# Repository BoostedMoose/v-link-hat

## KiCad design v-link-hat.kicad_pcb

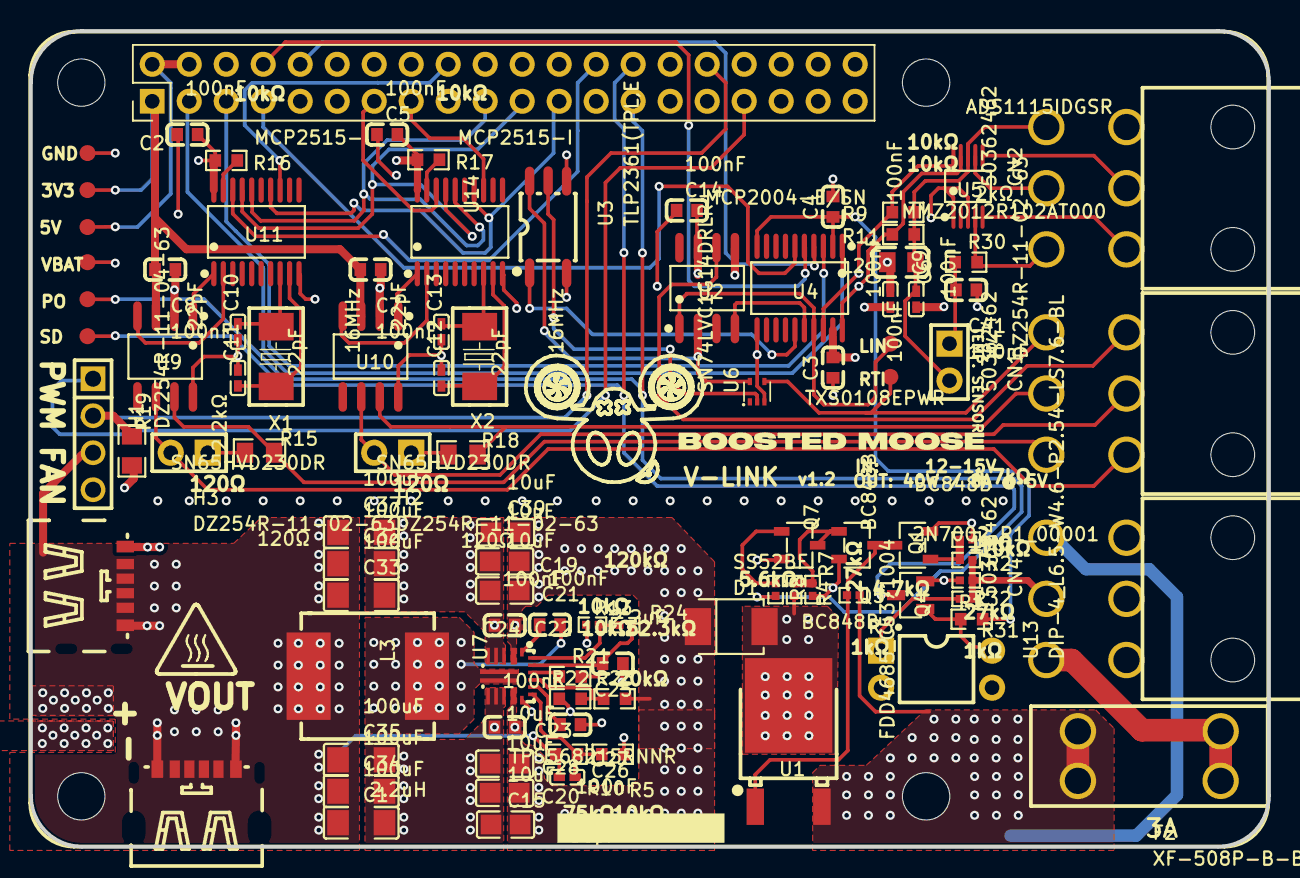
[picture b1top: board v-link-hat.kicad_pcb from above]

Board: 4 copper layers, 85.0 x 56.0 mm, 96 parts (0 on the bottom side), 69 nets.

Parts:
C1, C32, C33, C34, C35, C37: 100uF; C1206
C2, C3, C4, C5, C7, C8, C14, C22, C23, C24, C27, C41: 100nF; C0603
C6, C9: 100nF; C0402
C10, C11, C12, C13: 22pF; C0402
C15, C19, C20, C21, C28, C39: 10uF; C0805
C25: 2.2uF; C0603
C26: 50pF; C0402
CN1, CN2, CN4: 50362462; CONN-TH_50362462
D1: SS52BF; SMBF_L4.3-W3.6-LS5.3-RD
F2: XF-508P-B-B; FUSE-TH_4P-L16.0-W6.7
H1: DZ254R-11-04-63; HDR-TH_4P-P2.54-V-M
H2, H3, H4: DZ254R-11-02-63; HDR-TH_2P-P2.54-V-M-1
L2: MMZ2012R102AT000; L0805
L3: 2.2uH; IND-SMD_L8.0-W8.0-1
Pad_gge54079: Pad_gge54079
Pad_gge54130: Pad_gge54130
Pad_gge54154: Pad_gge54154
Pad_gge54178: Pad_gge54178
Pad_gge54202: Pad_gge54202
Pad_gge54226: Pad_gge54226
Pad_gge90525: Pad_gge90525
Pad_gge90570: Pad_gge90570
Q1, Q5, Q7: BC848B; SOT-23-3_L2.9-W1.6-P1.90-LS2.8-BR
Q4: 2N7002_R1_00001; SOT-23-3_L2.9-W1.3-P1.90-LS2.4-BR
R1: 1MΩ; R0402
R2, R8: 27kΩ; R0402
R3, R31: 1kΩ; R0402
R4, R6: 4.7kΩ; R0402
R5, R9, R11, R16, R17, R21, R22, R32: 10kΩ; R0603
R7: 5.6kΩ; R0402
R10: 75kΩ; R0603
R13: 120kΩ; R0402
R15, R18: 120Ω; R0805
R19: 2.2kΩ; R0805
R23: 52.3kΩ; R0603
R24: 20kΩ; R0402
R30: 2kΩ; R0603
U1: FDD4685_C5371004; TO-252-3_L6.6-W6.1-P4.57-LS9.9-BR-CW
U2: MCP2004-E/SN; SOIC-8_L4.9-W3.9-P1.27-LS6.0-BL
U3: TLP2361(TPL,E; OPTO-SMD-5_L3.7-W4.6-P1.27-LS7.0-BR
U4: TXS0108EPWR; TSSOP-20_L6.5-W4.4-P0.65-LS6.4-BL
U5: ADS1115IDGSR; MSOP-10_L3.0-W3.0-P0.50-LS5.0-BL
U6: SN74LVC1G14DRLR; SOT-553-5_L1.6-W1.2-P0.50-LS1.6-TL
U7: TPS568215RNNR; VQFN-HR-18_L3.5-W3.5-P0.55-BL_TPS56C215RNNR
U8: RASPBERRY PI 4B
U9, U10: SN65HVD230DR; SOIC-8_L4.9-W3.9-P1.27-LS6.0-BL
U11, U14: MCP2515-I; TSSOP-20_L6.5-W4.4-P0.65-LS6.4-BL
U13: DIP-4_L6.5-W4.6-P2.54-LS7.6-BL
USB1, USB2: TYPE-C 6P(073); TYPE-C-SMD_TYPE-C-6P
X1, X2: 16MHz; OSC-SMD_L5.0-W3.2

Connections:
3.3V_PI: C2.2, C4.2, C5.2, C7.2, C8.2, Pad_gge54130.1, R16.1, R17.1, R19.2, R32.2, U4.2, U4.10, U8.1, U8.17, U9.3, U10.3, U11.20, U14.20
5V_RPI: C3.1, C6.1, L2.1, Pad_gge54154.1, U2.2, U3.6, U4.19, U6.5, U8.2, U8.4
!RTI_RX_5V: U3.5, U6.2
AVDD: C9.2, CN2.4, H4.2, L2.2, R9.2, R11.2, U5.8
A_IN_0: CN2.6, R30.2, U5.4
A_IN_1: CN2.3, U5.5
A_IN_2: CN2.2, U5.6
A_IN_3: CN2.5, U5.7
C12_2: C12.2, U14.9, X2.2
C13_2: C13.2, U14.8, X2.1
CAN1_H: CN1.6, R15.1, U9.7
CAN1_L: CN1.3, H3.2, U9.6
CAN2_H: CN1.5, R18.1, U10.7
CAN2_L: CN1.2, H2.2, U10.6
CE1: U8.26, U11.18
CE2: U8.13, U14.18
FB: C26.1, R5.2, R10.1, U7.13
GND: C1.2, C2.1, C3.2, C4.1, C5.1, C6.2, C7.1, C8.1, C9.1, C10.1, C11.1, C12.1, C13.1, C14.1, C15.1, C19.1, C20.1, C21.1, C22.1, C23.1, C25.2, C27.1, C28.1, C32.2, C33.2, C34.2, C35.2, C37.2, C39.1, C41.1, CN2.1, CN4.1, CN4.2, CN4.3, H1.4, Pad_gge54079.1, Q1.2, Q4.2, Q5.2, Q7.2, R1.1, R4.2, R5.1, R6.2, R13.1, R22.1, U2.5, U3.3, U3.4, U4.11, U5.1, U5.3, U6.3, U7.3, U7.4, U7.5, U7.8, U7.9, U7.10, U7.12, U8.6, U8.9, U8.14, U8.20, U8.25, U8.30, U8.34, U8.39, U9.2, U9.8, U10.2, U10.8, U11.10, U13.2, U13.3, U14.10, USB1.A12, USB1.B12, USB2.A12, USB2.B12
GPIO_POWEROFF: Pad_gge54202.1, R8.2, U8.27
GPIO_SHUTDOWN: Pad_gge54226.1, Q4.3, U8.28
H4_1: C41.2, H4.1, R30.1
IGN: CN4.5, R1.2, R2.1, R31.1
IGN_HAT: Q4.1, R32.1, U13.4
IGN_OPTO: R31.2, U13.1
INT_1: U8.18, U11.13
INT_2: U8.15, U14.13
LIN: CN1.1, U2.6
LIN_RX_3V: U4.4, U8.10
LIN_RX_5V: Pad_gge90525.1, U2.1, U4.17
LIN_TX_3V: U4.5, U8.8
LIN_TX_5V: U2.4, U4.16
MISO: U8.21, U11.17, U14.17
MOSI: U8.19, U11.16, U14.16
PWM: H1.1, U8.33
R2_2: Q1.1, R2.2, R6.1
R3_1: F2.2, F2.3, R3.1, U1.3
R3_2: Q1.3, Q5.3, R3.2, U1.1
R4_1: Q5.1, Q7.3, R4.1, R7.2
R7_1: D1.2, R7.1, U1.2
R8_1: Q7.1, R8.1
R15_2: H3.1, R15.2
R17_2: R17.2, U14.19
R18_2: H2.1, R18.2
RTI_RX: CN1.4, Pad_gge90570.1, U6.4
RTI_RX_3V: U4.6, U8.7
RTI_RX_5V: U3.1, U4.15
SCLK: U8.23, U11.14, U14.14
SCL_3V: U4.3, U8.5
SCL_5V: R9.1, U4.18, U5.10
SDA_3V: U4.1, U8.3
SDA_5V: R11.1, U4.20, U5.9
SW: C24.2, L3.2, U7.6, U7.7
TACHO: H1.2, R19.1, U8.32
U7_1: C24.1, U7.1
U7_14: C27.2, U7.14
U7_15: R22.2, R23.1, U7.15
U7_16: R21.1, U7.16
U7_17: C25.1, R21.2, R24.1, U7.17
U7_18: R13.2, R24.2, U7.18
U11_1: U9.1, U11.1
U11_2: U9.4, U11.2
U11_8: C10.2, U11.8, X1.1
U11_9: C11.2, U11.9, X1.2
U11_19: R16.2, U11.19
U14_1: U10.1, U14.1
U14_2: U10.4, U14.2
VBAT: CN4.6, F2.1, F2.4
VDD: C14.2, C15.2, C19.2, C20.2, C21.2, C22.2, C23.2, C28.2, C39.2, D1.1, Pad_gge54178.1, R23.2, U2.7, U7.2, U7.11
VOUT: C1.1, C26.2, C32.1, C33.1, C34.1, C35.1, C37.1, CN4.4, H1.3, L3.1, R10.2, USB1.A9, USB1.B9, USB2.A9, USB2.B9

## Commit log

2025-05-16 Initial upload of KiCad files
